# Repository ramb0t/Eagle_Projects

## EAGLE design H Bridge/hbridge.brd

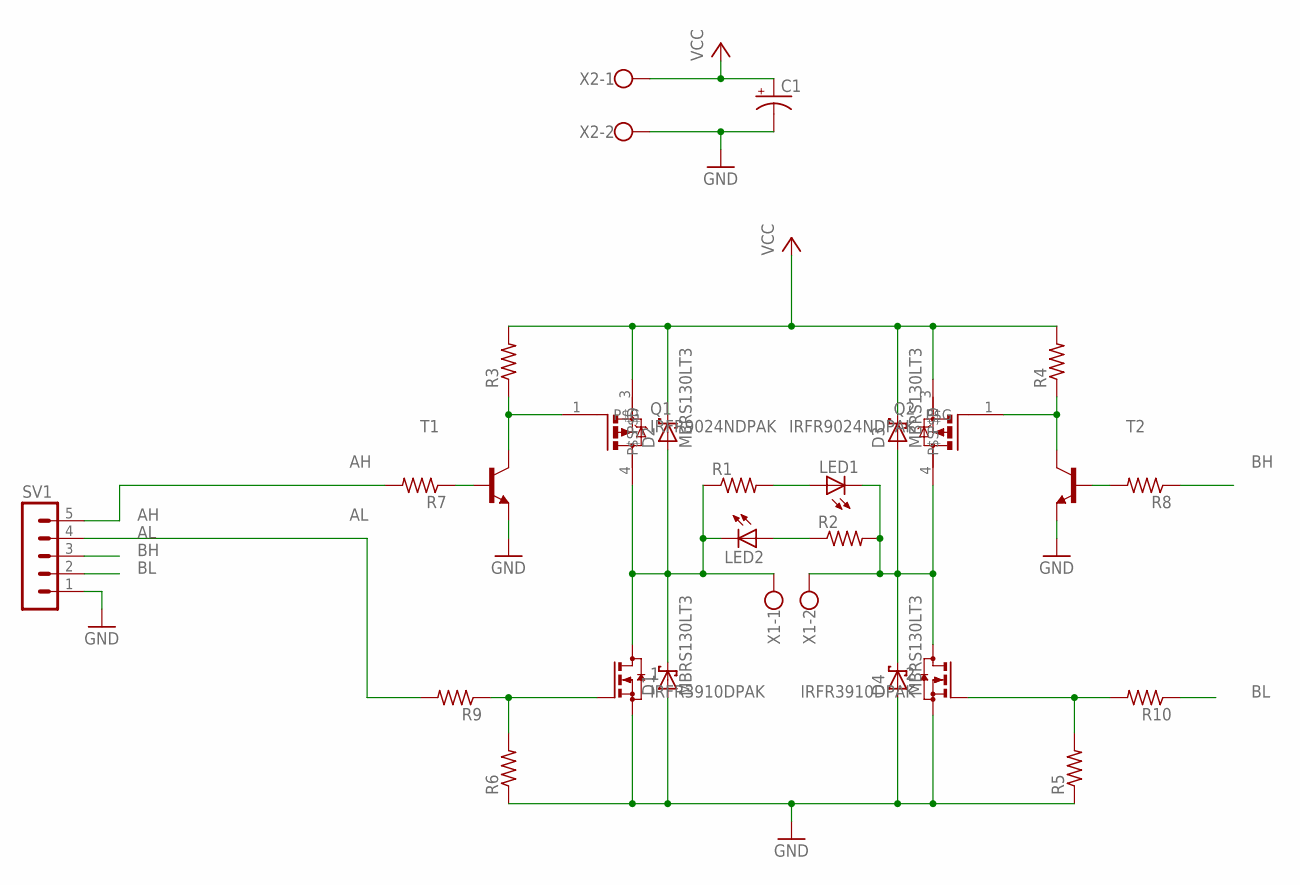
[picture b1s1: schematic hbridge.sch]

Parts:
1, 2: IRFR3910DPAK; D-PAK_TO252AA
C1: CPOL-USE5-10.5; E5-10,5
D1, D2, D3, D4: MBRS130LT3; SMB
LED1, LED2: LEDCHIP-LED0805; CHIP-LED0805
Q1, Q2: IRFR9024NDPAK; D-PAK_TO252AA
R1, R2, R3, R4, R5, R6, R7, R8, R9, R10: R-US_R0805; R0805
SV1: MA05-1
T1, T2: MMBT2222ALT1-NPN-SOT23-BEC; SOT23-BEC
X1: W237-102
X2: W237-102; MPN 237-102

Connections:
AH: R7.2, SV1.5
AL: R9.2, SV1.4
BH: R8.1, SV1.3
BL: R10.1, SV1.2
GND: 1.3 (S), 2.3 (S), C1.-, D1.A, D4.A, R5.1, R6.1, SV1.1, T1.E, T2.E, X2.2
M1: 1.4 (D), D1.C, D2.A, LED2.C, Q1.4 (P$D), R1.1, X1.1
M2: 2.4 (D), D3.A, D4.C, LED1.C, Q2.4 (P$D), R2.2, X1.2
unnamed: LED2.A, R2.1
unnamed: LED1.A, R1.2
unnamed: 1.1 (G), R6.2, R9.1
unnamed: Q1.1 (P$G), R3.1, T1.C
unnamed: Q2.1 (P$G), R4.1, T2.C
unnamed: R7.1, T1.B
unnamed: R8.2, T2.B
NS12: 2.1 (G), R5.2, R10.2
VCC: C1.+, D2.C, D3.C, Q1.3 (P$S), Q2.3 (P$S), R3.2, R4.2, X2.1

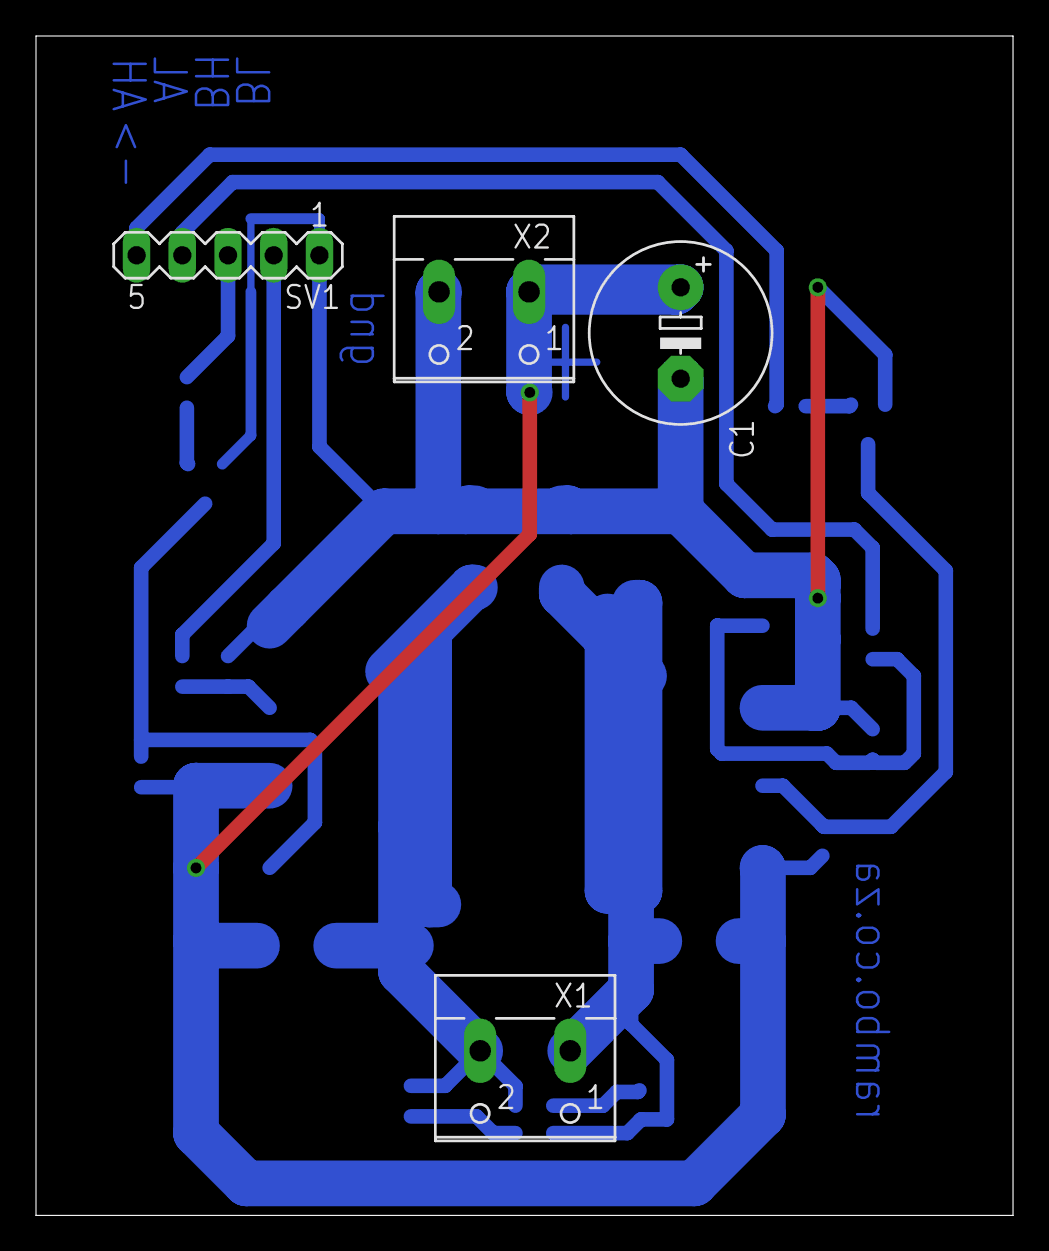
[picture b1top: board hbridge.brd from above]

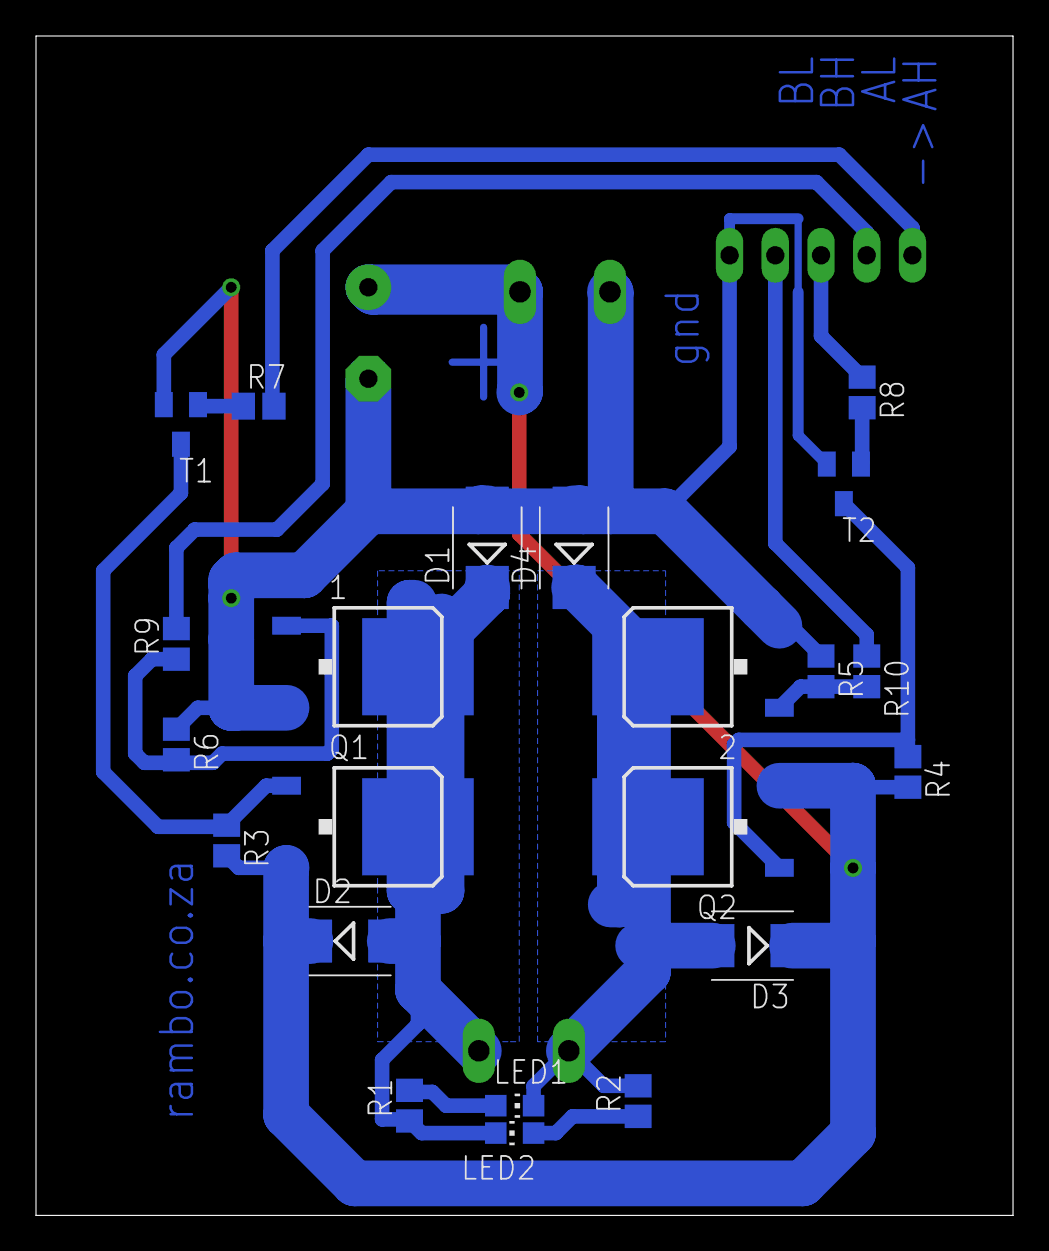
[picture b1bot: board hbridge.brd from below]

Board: 2 copper layers, 54.3 x 65.5 mm, 26 parts (22 on the bottom side), 16 nets.

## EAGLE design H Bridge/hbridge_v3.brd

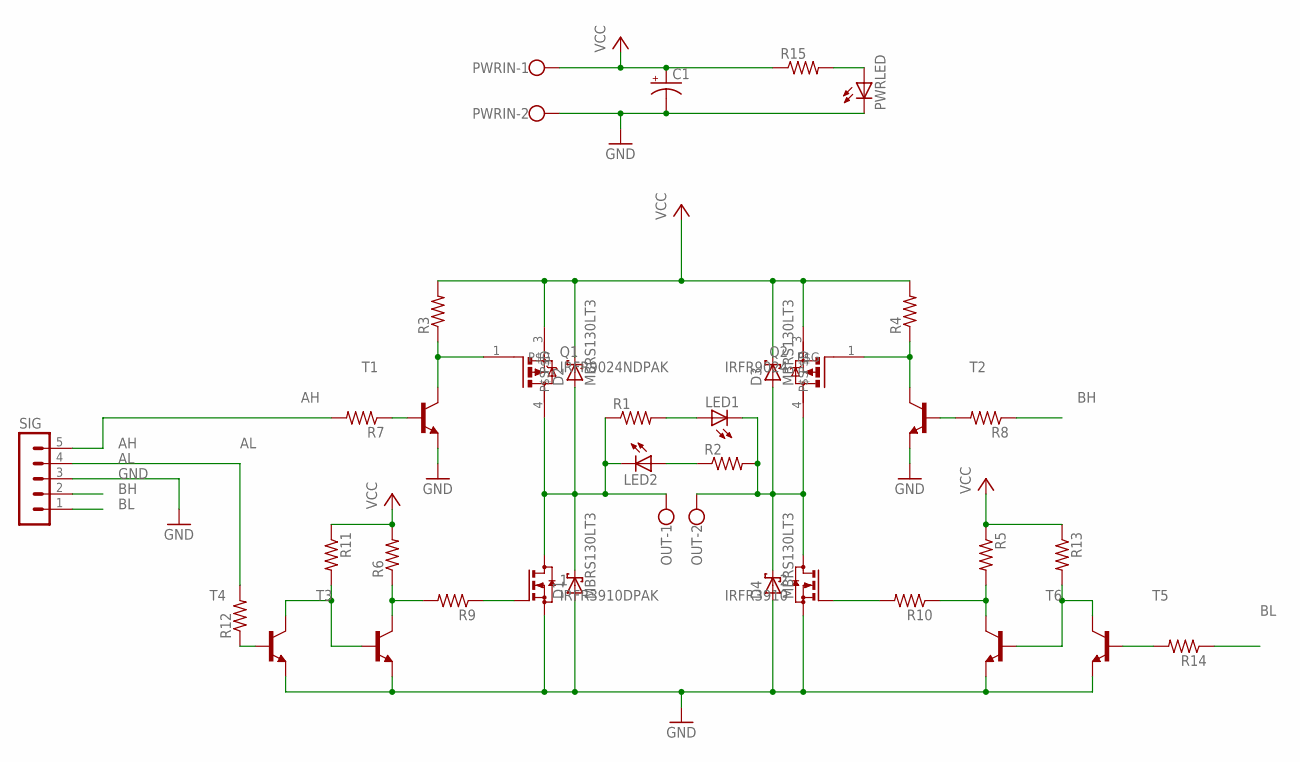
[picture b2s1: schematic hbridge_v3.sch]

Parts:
1: IRFR3910DPAK; D-PAK_TO252AA
2: IRFR3910; D-PAK_TO252AA
C1: CPOL-USE5-10.5; E5-10,5
D1, D2, D3, D4: MBRS130LT3; SMB
LED1, LED2: LEDCHIP-LED0805; CHIP-LED0805
OUT: W237-102
PWRIN: W237-102; MPN 237-102
PWRLED: LEDCHIP-LED0805; CHIP-LED0805
Q1: IRFR9024NDPAK; D-PAK_TO252AA
Q2: IRFR9024; D-PAK_TO252AA
R1, R2, R3, R4, R5, R6, R7, R8, R9, R10, R11, R12, R13, R14, R15: R-US_R0805; R0805
SIG: MA05-1
T1, T2, T3, T4, T5, T6: MMBT2222ALT1-NPN-SOT23-BEC; SOT23-BEC

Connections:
AH: R7.2, SIG.5
AL: R12.2, SIG.4
BH: R8.1, SIG.2
BL: R14.1, SIG.1
GND: 1.3 (S), 2.3 (S), C1.-, D1.A, D4.A, PWRIN.2, PWRLED.C, SIG.3, T1.E, T2.E, T3.E, T4.E, T5.E, T6.E
M1: 1.4 (D), D1.C, D2.A, LED2.C, OUT.1, Q1.4 (P$D), R1.1
M2: 2.4 (D), D3.A, D4.C, LED1.C, OUT.2, Q2.4 (P$D), R2.2
unnamed: LED2.A, R2.1
unnamed: LED1.A, R1.2
unnamed: 1.1 (G), R9.1
unnamed: R6.1, R9.2, T3.C
unnamed: R11.2, T3.B, T4.C
unnamed: Q1.1 (P$G), R3.1, T1.C
unnamed: Q2.1 (P$G), R4.1, T2.C
unnamed: 2.1 (G), R10.2
unnamed: R7.1, T1.B
unnamed: R12.1, T4.B
unnamed: R8.2, T2.B
unnamed: R5.2, R10.1, T6.C
unnamed: R13.2, T5.C, T6.B
unnamed: R14.2, T5.B
unnamed: PWRLED.A, R15.2
VCC: C1.+, D2.C, D3.C, PWRIN.1, Q1.3 (P$S), Q2.3 (P$S), R3.2, R4.2, R5.1, R6.2, R11.1, R13.1, R15.1

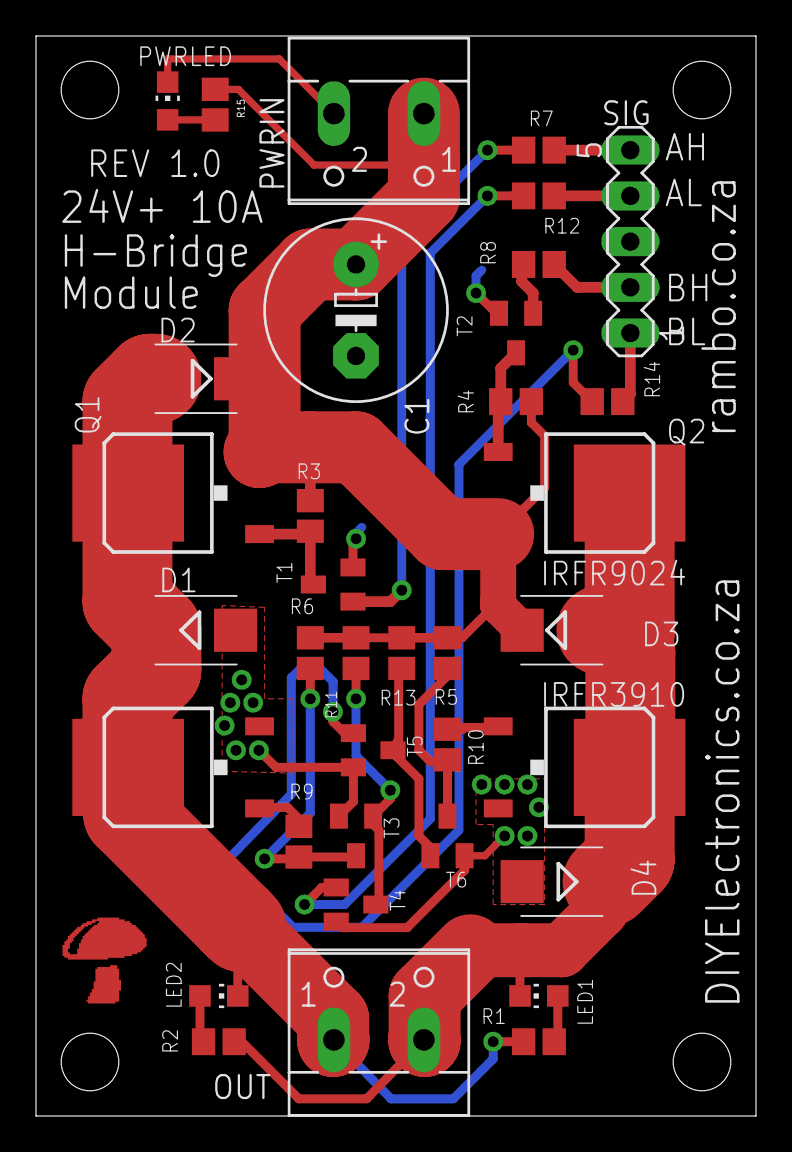
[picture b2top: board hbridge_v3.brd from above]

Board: 2 copper layers, 40.0 x 60.0 mm, 36 parts (0 on the bottom side), 23 nets.

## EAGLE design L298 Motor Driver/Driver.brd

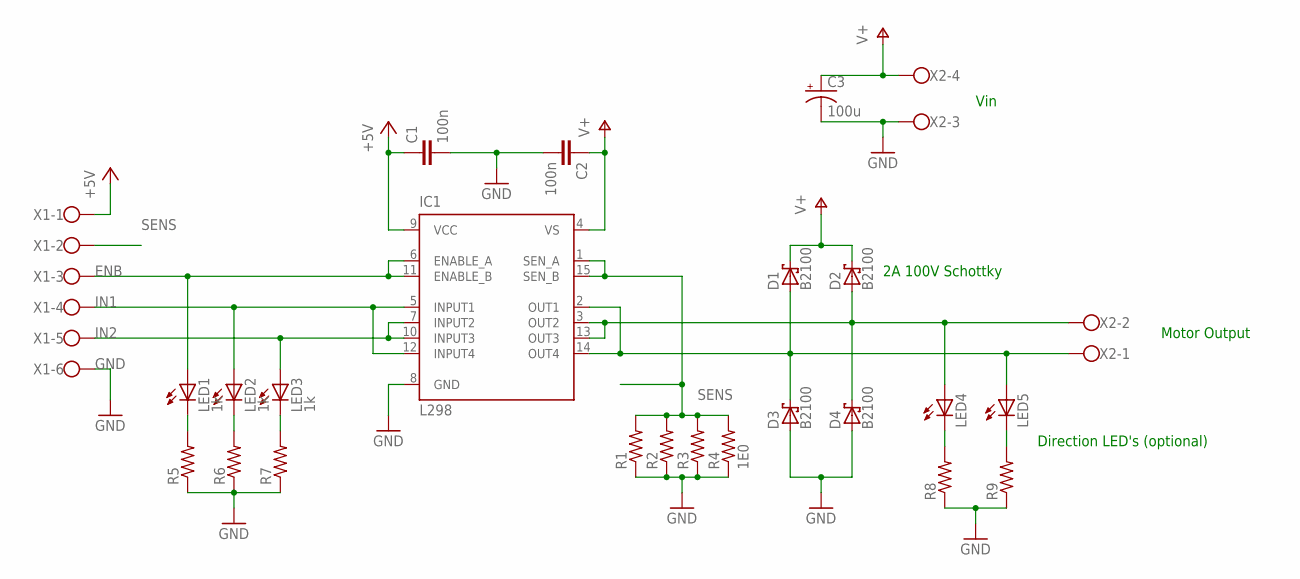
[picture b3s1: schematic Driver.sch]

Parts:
C1, C2: 100n; C0805K
C3: 100u; E7,5-16
D1, D2, D3, D4: B2100; SMC
IC1: L298; MULTIWATT-15
LED1, LED2, LED3: 1k; LED3MM
LED4, LED5: LED3MM
R1, R2, R3: R-US_R2512; R2512
R4: 1E0; R2512
R5, R6, R7, R8, R9: R-US_R0805; R0805
X1: W237-6
X2: W237-4

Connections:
+5V: C1.1, IC1.9 (VCC), X1.1
ENB: IC1.6 (ENABLE_A), IC1.11 (ENABLE_B), LED1.A, X1.3
GND: C1.2, C2.2, C3.-, D3.A, D4.A, IC1.8 (GND), R1.1, R2.1, R3.1, R4.1, R5.1, R6.1, R7.1, R8.1, R9.1, X1.6, X2.3
IN1: IC1.5 (INPUT1), IC1.12 (INPUT4), LED2.A, X1.4
IN2: IC1.7 (INPUT2), IC1.10 (INPUT3), LED3.A, X1.5
unnamed: LED4.K (C), R8.2
unnamed: LED5.K (C), R9.2
unnamed: LED1.K (C), R5.2
unnamed: LED2.K (C), R6.2
unnamed: LED3.K (C), R7.2
OUT1: D1.A, D3.C, IC1.2 (OUT1), IC1.14 (OUT4), LED5.A, X2.1
OUT2: D2.A, D4.C, IC1.3 (OUT2), IC1.13 (OUT3), LED4.A, X2.2
SENS: IC1.1 (SEN_A), IC1.15 (SEN_B), R1.2, R2.2, R3.2, R4.2, X1.2
V+: C2.1, C3.+, D1.C, D2.C, IC1.4 (VS), X2.4

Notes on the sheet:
2A 100V Schottky
Motor Output
Vin
Direction LED's (optional)

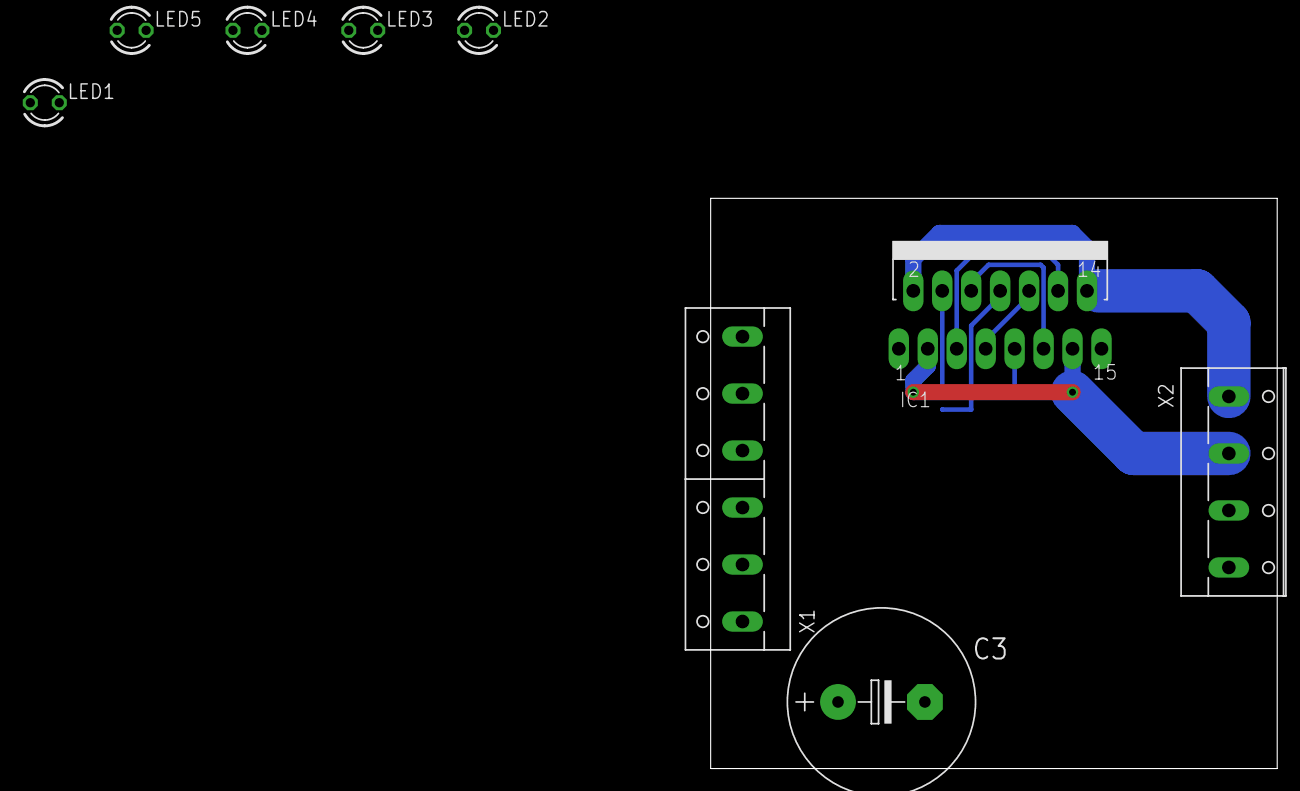
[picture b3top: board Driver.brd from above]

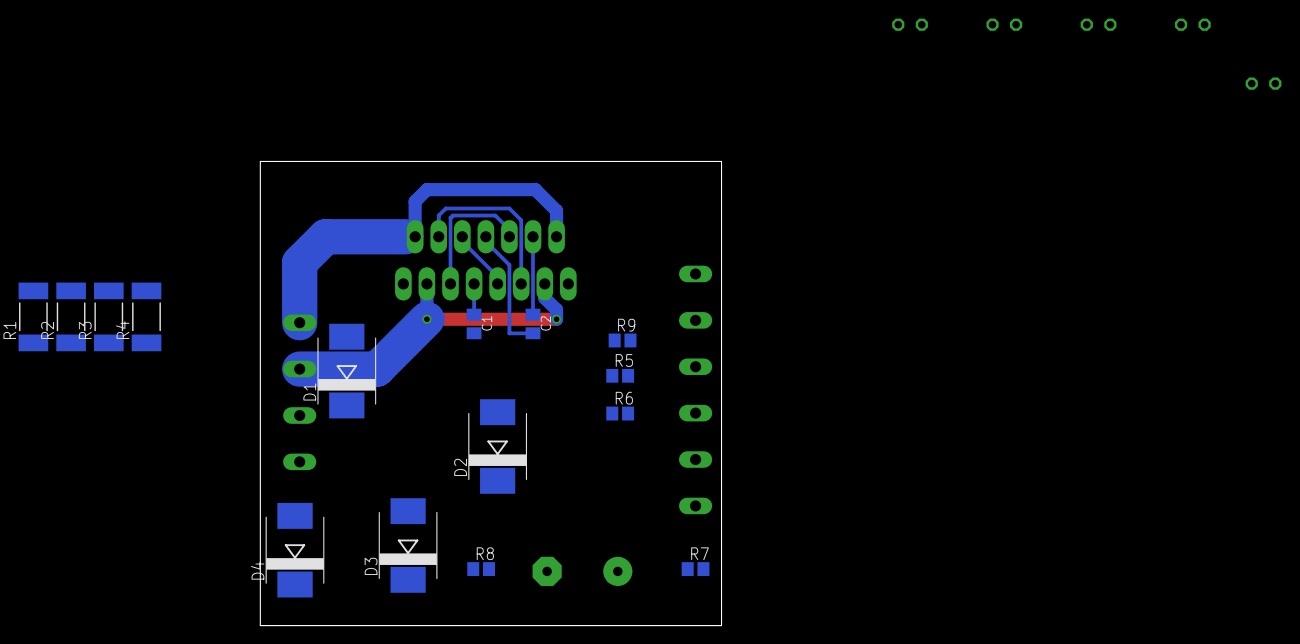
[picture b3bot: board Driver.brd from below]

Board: 2 copper layers, 49.7 x 50.0 mm, 24 parts (15 on the bottom side), 14 nets.

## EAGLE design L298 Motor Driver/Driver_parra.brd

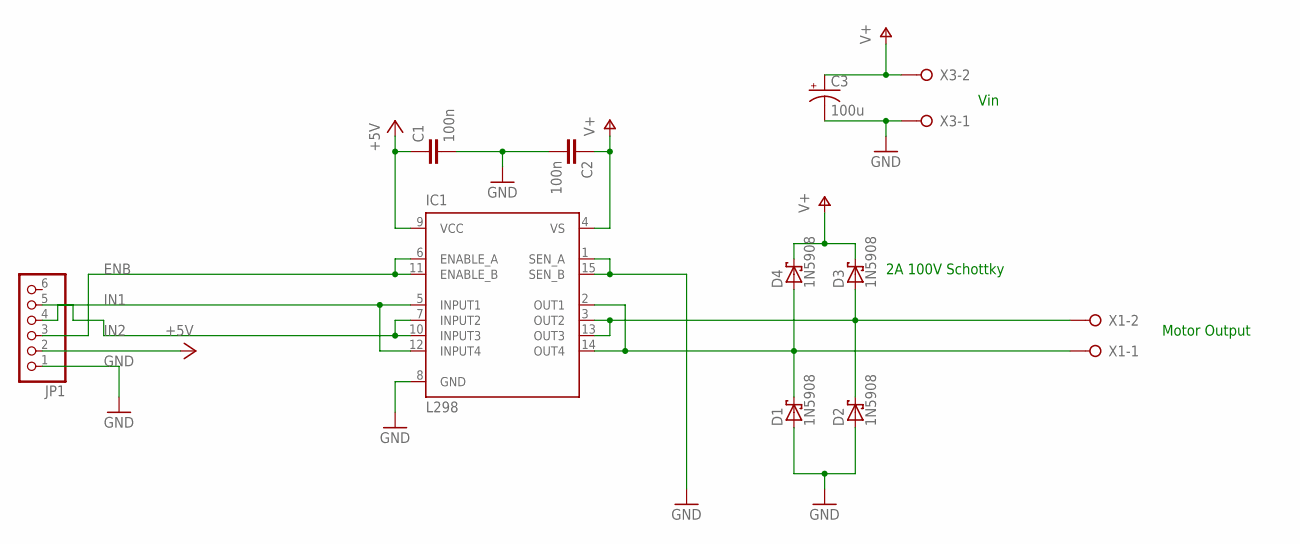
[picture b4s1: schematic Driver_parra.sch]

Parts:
C1, C2: 100n; C0805K
C3: 100u; E7,5-16
D1, D2, D3, D4: 1N5908; C4111-15
IC1: L298; MULTIWATT-15
JP1: PINHD-1X6; 1X06
X1, X3: W237-02P; W237-132

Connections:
+5V: C1.1, IC1.9 (VCC), JP1.2
ENB: IC1.6 (ENABLE_A), IC1.11 (ENABLE_B), JP1.3
GND: C1.2, C2.2, C3.-, D1.A, D2.A, IC1.1 (SEN_A), IC1.8 (GND), IC1.15 (SEN_B), JP1.1, X3.1
IN1: IC1.5 (INPUT1), IC1.12 (INPUT4), JP1.4
IN2: IC1.7 (INPUT2), IC1.10 (INPUT3), JP1.5
OUT1: D1.C, D4.A, IC1.2 (OUT1), IC1.14 (OUT4), X1.1
OUT2: D2.C, D3.A, IC1.3 (OUT2), IC1.13 (OUT3), X1.2
V+: C2.1, C3.+, D3.C, D4.C, IC1.4 (VS), X3.2

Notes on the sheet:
2A 100V Schottky
Motor Output
Vin

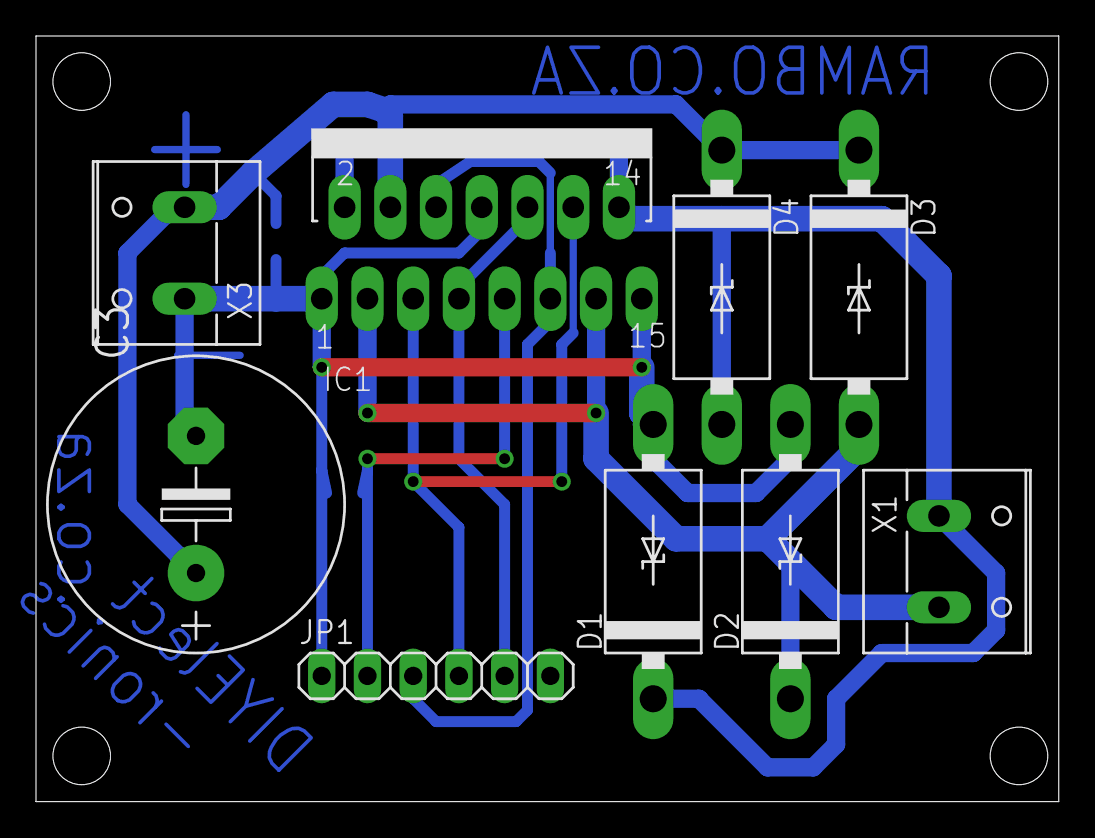
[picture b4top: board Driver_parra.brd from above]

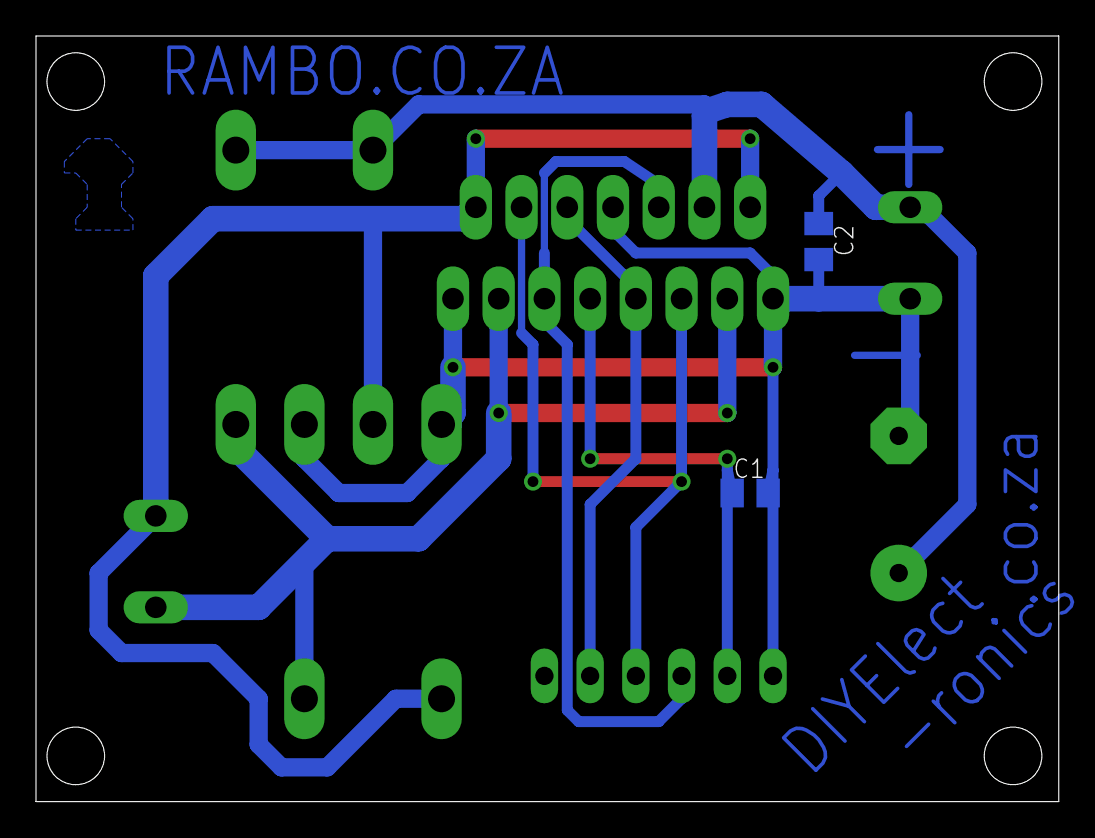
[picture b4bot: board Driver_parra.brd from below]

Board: 2 copper layers, 56.8 x 42.5 mm, 11 parts (2 on the bottom side), 8 nets.

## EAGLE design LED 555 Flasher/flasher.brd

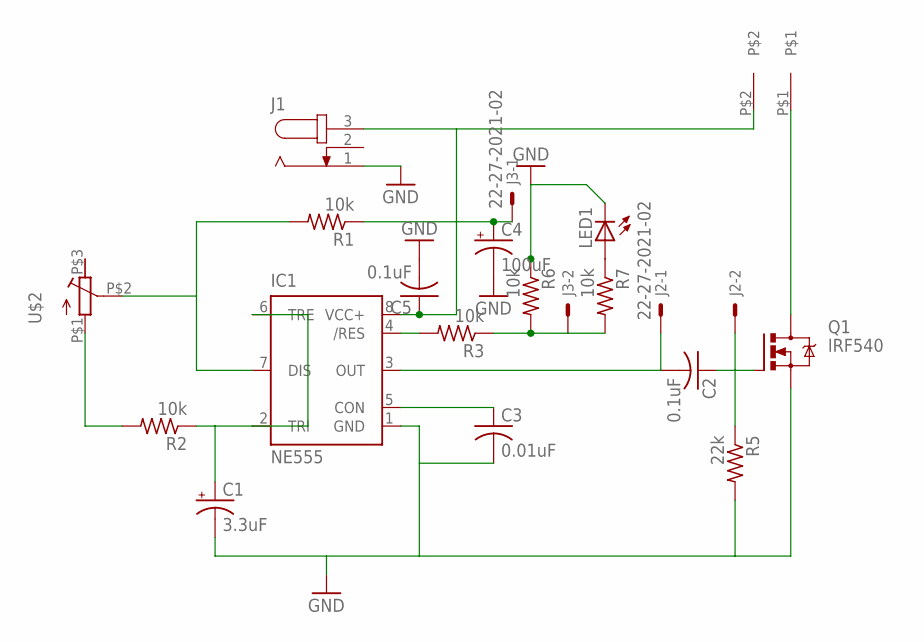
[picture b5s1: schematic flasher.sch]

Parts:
C1: 3.3uF; E2,5-5
C2: 0.1uF; C050-030X075
C3: 0.01uF; C025-025X050
C4: 100uF; E2,5-5
C5: 0.1uF; C025-025X050
IC1: NE555; DIL-08
J1: JACK-PLUG0; SPC4077
J2, J3: 22-27-2021-02; 6410-02
LED1: LED5MM
Q1: IRF540; TO220BV
R1, R2, R3, R6, R7: 10k; 0207/10
R5: 22k; 0207/10
U$1: DG301-5.0
U$2: PANELMOUNT_POT

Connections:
GND: C1.-, C3.2, C4.-, C5.2, IC1.1 (GND), J1.1, LED1.K (C), Q1.S, R5.2, R6.1
unnamed: IC1.7 (DIS), R1.2, U$2.P$2 (2)
unnamed: C1.+, IC1.2 (TRI), IC1.6 (TRE), R2.1
unnamed: R2.2, U$2.P$1 (1)
unnamed: C2.1, J2.2, Q1.G, R5.1
unnamed: C3.1, IC1.5 (CON)
unnamed: IC1.4 (/RES), R3.2
unnamed: C2.2, IC1.3 (OUT), J2.1
unnamed: J3.2, R3.1, R6.2, R7.2
unnamed: Q1.D, U$1.P$1
unnamed: LED1.A, R7.1
VCC: C4.+, C5.1, IC1.8 (VCC+), J1.3, J3.1, R1.1, U$1.P$2

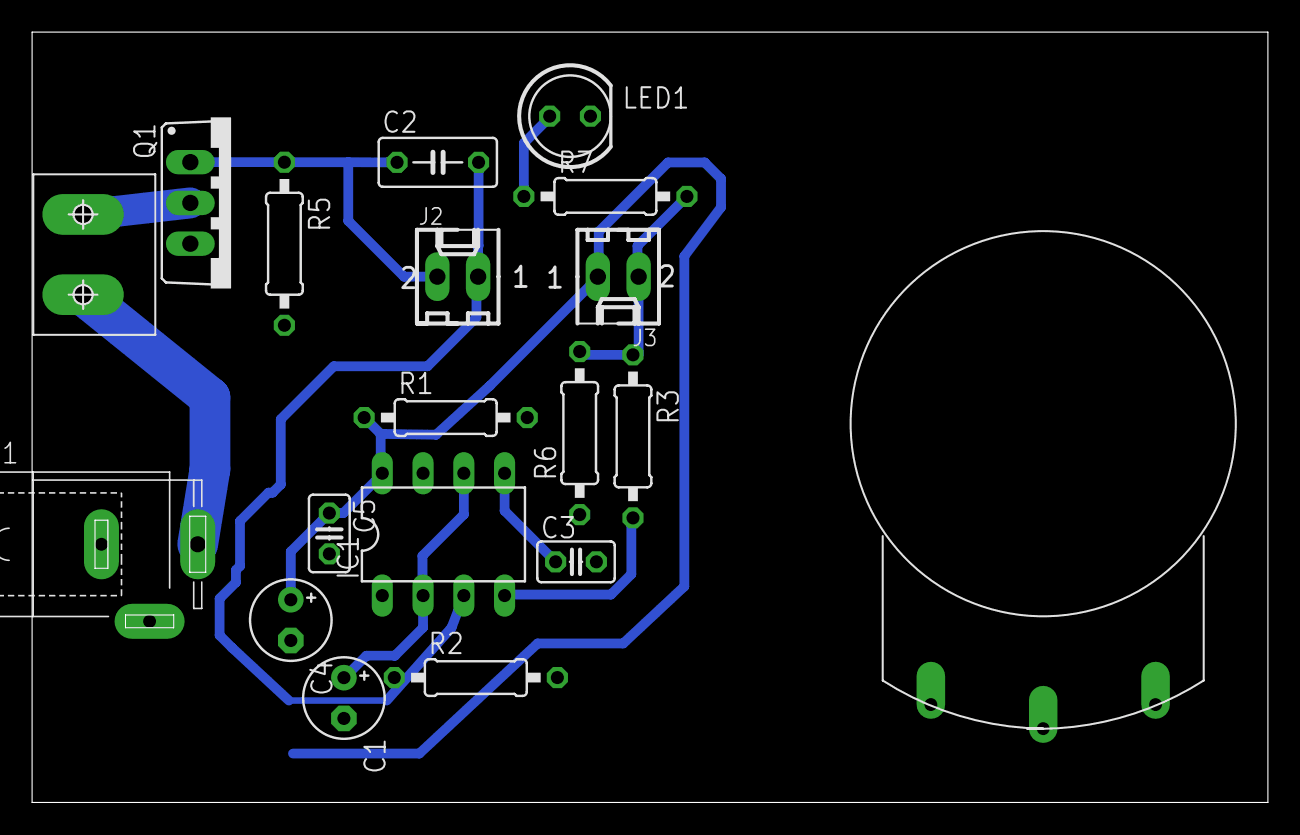
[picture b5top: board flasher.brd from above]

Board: 2 copper layers, 77.0 x 48.0 mm, 19 parts (0 on the bottom side), 12 nets.
